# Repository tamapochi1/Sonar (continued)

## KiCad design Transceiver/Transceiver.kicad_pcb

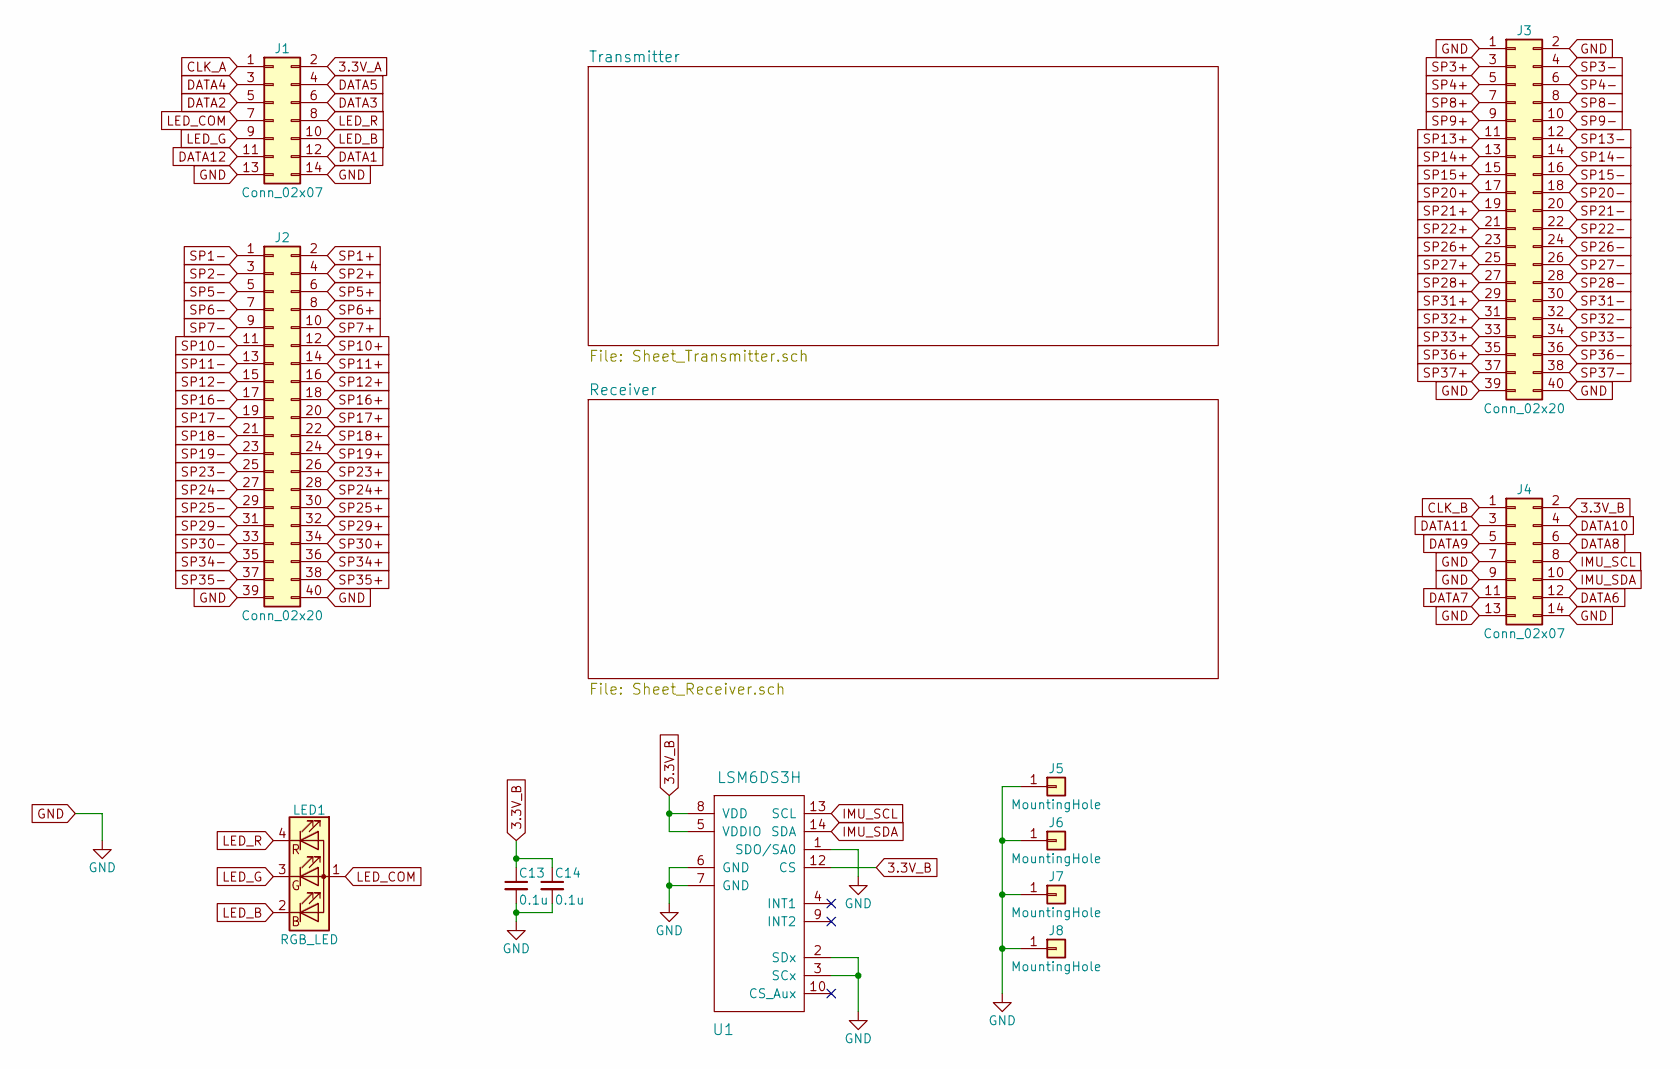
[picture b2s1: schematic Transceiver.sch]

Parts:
C13, C14: 0.1u; C_0603_HandSoldering
J1, J4: Conn_02x07; Pin_Header_Straight_2x07_Pitch2.54mm
J2, J3: Conn_02x20; Pin_Header_Straight_2x20_Pitch2.54mm
J5, J6, J7, J8: MountingHole; MountingHole_3.2mm_M3_Pad
LED1: RGB_LED; LED_Cree-PLCC4_2x2mm_CW
U1: LSM6DS3H; Bosch_LGA-14_3x2.5mm_Pitch0.5mm

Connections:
3.3V_A: J1.2; also elsewhere on the board
3.3V_B: C13.1, C14.1, J4.2, U1.5 (VDDIO), U1.8 (VDD), U1.12 (CS); also elsewhere on the board
CLK_A: J1.1; also elsewhere on the board
CLK_B: J4.1; also elsewhere on the board
DATA1: J1.12; also elsewhere on the board
DATA2: J1.5; also elsewhere on the board
DATA3: J1.6; also elsewhere on the board
DATA4: J1.3; also elsewhere on the board
DATA5: J1.4; also elsewhere on the board
DATA6: J4.12; also elsewhere on the board
DATA7: J4.11; also elsewhere on the board
DATA8: J4.6; also elsewhere on the board
DATA9: J4.5; also elsewhere on the board
DATA10: J4.4; also elsewhere on the board
DATA11: J4.3; also elsewhere on the board
DATA12: J1.11; also elsewhere on the board
GND: C13.2, C14.2, J1.13, J1.14, J2.39, J2.40, J3.1, J3.2, J3.39, J3.40, J4.7, J4.9, J4.13, J4.14, J5.1, J6.1, J7.1, J8.1, U1.1 (SDO/SA0), U1.2 (SDx), U1.3 (SCx), U1.6 (GND), U1.7 (GND); also elsewhere on the board
IMU_SCL: J4.8, U1.13 (SCL)
IMU_SDA: J4.10, U1.14 (SDA)
LED_B: J1.10, LED1.2 (BK)
LED_COM: J1.7, LED1.1 (A)
LED_G: J1.9, LED1.3 (GK)
LED_R: J1.8, LED1.4 (RK)
SP1+: J2.2; also elsewhere on the board
SP1-: J2.1; also elsewhere on the board
SP2+: J2.4; also elsewhere on the board
SP2-: J2.3; also elsewhere on the board
SP3+: J3.3; also elsewhere on the board
SP3-: J3.4; also elsewhere on the board
SP4+: J3.5; also elsewhere on the board
SP4-: J3.6; also elsewhere on the board
SP5+: J2.6; also elsewhere on the board
SP5-: J2.5; also elsewhere on the board
SP6+: J2.8; also elsewhere on the board
SP6-: J2.7; also elsewhere on the board
SP7+: J2.10; also elsewhere on the board
SP7-: J2.9; also elsewhere on the board
SP8+: J3.7; also elsewhere on the board
SP8-: J3.8; also elsewhere on the board
SP9+: J3.9; also elsewhere on the board
SP9-: J3.10; also elsewhere on the board
SP10+: J2.12; also elsewhere on the board
SP10-: J2.11; also elsewhere on the board
SP11+: J2.14; also elsewhere on the board
SP11-: J2.13; also elsewhere on the board
SP12+: J2.16; also elsewhere on the board
SP12-: J2.15; also elsewhere on the board
SP13+: J3.11; also elsewhere on the board
SP13-: J3.12; also elsewhere on the board
SP14+: J3.13; also elsewhere on the board
SP14-: J3.14; also elsewhere on the board
SP15+: J3.15; also elsewhere on the board
SP15-: J3.16; also elsewhere on the board
SP16+: J2.18; also elsewhere on the board
SP16-: J2.17; also elsewhere on the board
SP17+: J2.20; also elsewhere on the board
SP17-: J2.19; also elsewhere on the board
SP18+: J2.22; also elsewhere on the board
SP18-: J2.21; also elsewhere on the board
SP19+: J2.24; also elsewhere on the board
SP19-: J2.23; also elsewhere on the board
SP20+: J3.17; also elsewhere on the board
SP20-: J3.18; also elsewhere on the board
SP21+: J3.19; also elsewhere on the board
SP21-: J3.20; also elsewhere on the board
SP22+: J3.21; also elsewhere on the board
SP22-: J3.22; also elsewhere on the board
SP23+: J2.26; also elsewhere on the board
SP23-: J2.25; also elsewhere on the board
SP24+: J2.28; also elsewhere on the board
SP24-: J2.27; also elsewhere on the board
SP25+: J2.30; also elsewhere on the board
SP25-: J2.29; also elsewhere on the board
SP26+: J3.23; also elsewhere on the board
SP26-: J3.24; also elsewhere on the board
SP27+: J3.25; also elsewhere on the board
SP27-: J3.26; also elsewhere on the board
SP28+: J3.27; also elsewhere on the board
SP28-: J3.28; also elsewhere on the board
SP29+: J2.32; also elsewhere on the board
SP29-: J2.31; also elsewhere on the board
SP30+: J2.34; also elsewhere on the board
SP30-: J2.33; also elsewhere on the board
SP31+: J3.29; also elsewhere on the board
SP31-: J3.30; also elsewhere on the board
SP32+: J3.31; also elsewhere on the board
SP32-: J3.32; also elsewhere on the board
SP33+: J3.33; also elsewhere on the board
SP33-: J3.34; also elsewhere on the board
SP34+: J2.36; also elsewhere on the board
SP34-: J2.35; also elsewhere on the board
SP35+: J2.38; also elsewhere on the board
SP35-: J2.37; also elsewhere on the board
SP36+: J3.35; also elsewhere on the board
SP36-: J3.36; also elsewhere on the board
SP37+: J3.37; also elsewhere on the board
SP37-: J3.38; also elsewhere on the board

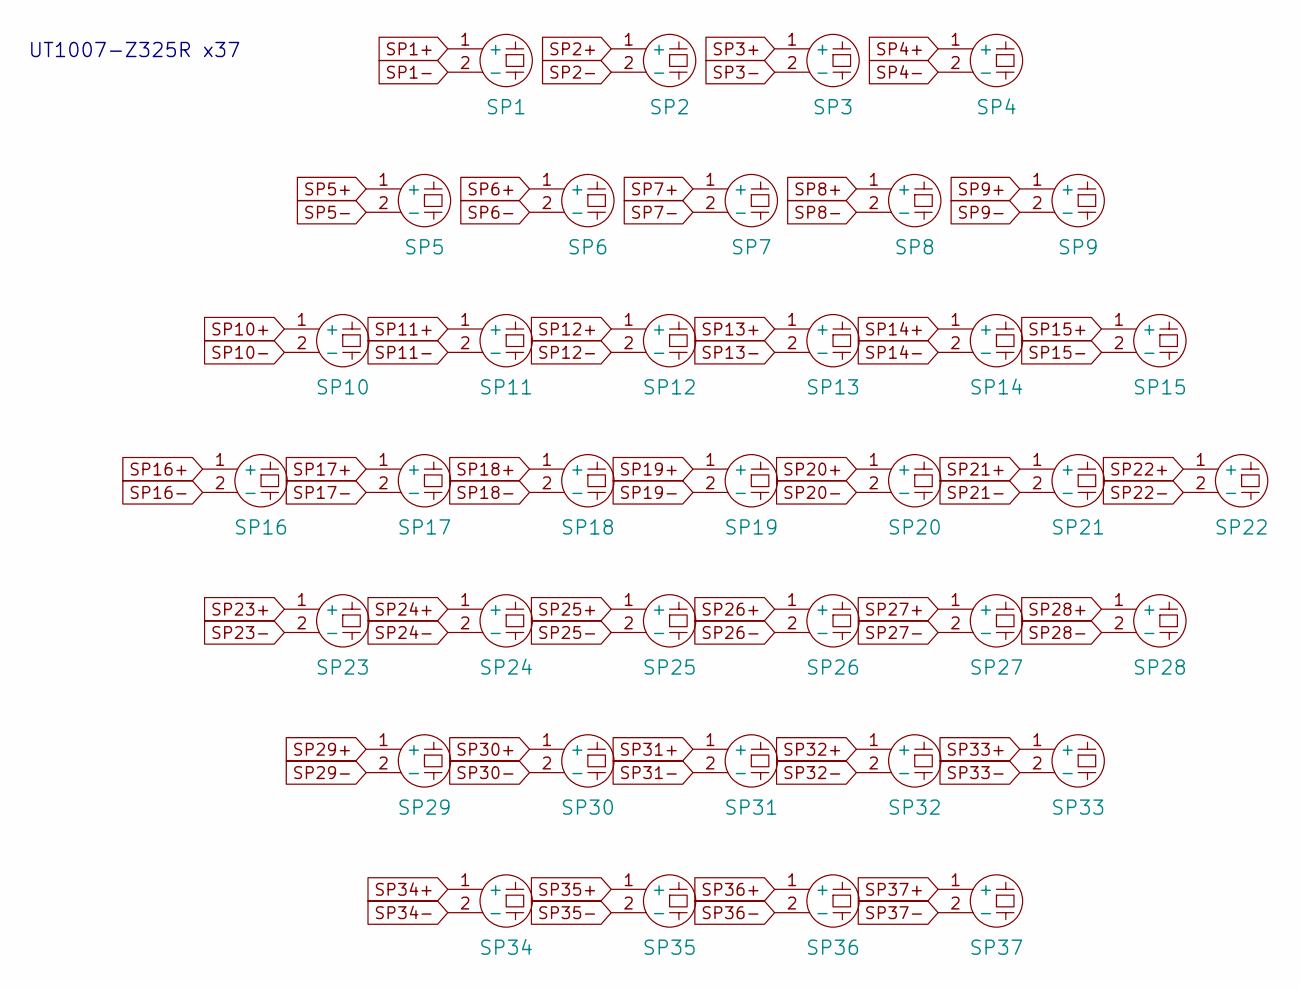
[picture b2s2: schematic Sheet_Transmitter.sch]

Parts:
SP1, SP2, SP3, SP4, SP5, SP6, SP7, SP8, SP9, SP10, SP11, SP12, SP13, SP14, SP15, SP16, SP17, SP18, SP19, SP20, SP21, SP22, SP23, SP24, SP25, SP26, SP27, SP28, SP29, SP30, SP31, SP32, SP33, SP34, SP35, SP36, SP37: UT1007-Z325R

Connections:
SP1+: SP1.1 (+); also elsewhere on the board
SP1-: SP1.2 (-); also elsewhere on the board
SP2+: SP2.1 (+); also elsewhere on the board
SP2-: SP2.2 (-); also elsewhere on the board
SP3+: SP3.1 (+); also elsewhere on the board
SP3-: SP3.2 (-); also elsewhere on the board
SP4+: SP4.1 (+); also elsewhere on the board
SP4-: SP4.2 (-); also elsewhere on the board
SP5+: SP5.1 (+); also elsewhere on the board
SP5-: SP5.2 (-); also elsewhere on the board
SP6+: SP6.1 (+); also elsewhere on the board
SP6-: SP6.2 (-); also elsewhere on the board
SP7+: SP7.1 (+); also elsewhere on the board
SP7-: SP7.2 (-); also elsewhere on the board
SP8+: SP8.1 (+); also elsewhere on the board
SP8-: SP8.2 (-); also elsewhere on the board
SP9+: SP9.1 (+); also elsewhere on the board
SP9-: SP9.2 (-); also elsewhere on the board
SP10+: SP10.1 (+); also elsewhere on the board
SP10-: SP10.2 (-); also elsewhere on the board
SP11+: SP11.1 (+); also elsewhere on the board
SP11-: SP11.2 (-); also elsewhere on the board
SP12+: SP12.1 (+); also elsewhere on the board
SP12-: SP12.2 (-); also elsewhere on the board
SP13+: SP13.1 (+); also elsewhere on the board
SP13-: SP13.2 (-); also elsewhere on the board
SP14+: SP14.1 (+); also elsewhere on the board
SP14-: SP14.2 (-); also elsewhere on the board
SP15+: SP15.1 (+); also elsewhere on the board
SP15-: SP15.2 (-); also elsewhere on the board
SP16+: SP16.1 (+); also elsewhere on the board
SP16-: SP16.2 (-); also elsewhere on the board
SP17+: SP17.1 (+); also elsewhere on the board
SP17-: SP17.2 (-); also elsewhere on the board
SP18+: SP18.1 (+); also elsewhere on the board
SP18-: SP18.2 (-); also elsewhere on the board
SP19+: SP19.1 (+); also elsewhere on the board
SP19-: SP19.2 (-); also elsewhere on the board
SP20+: SP20.1 (+); also elsewhere on the board
SP20-: SP20.2 (-); also elsewhere on the board
SP21+: SP21.1 (+); also elsewhere on the board
SP21-: SP21.2 (-); also elsewhere on the board
SP22+: SP22.1 (+); also elsewhere on the board
SP22-: SP22.2 (-); also elsewhere on the board
SP23+: SP23.1 (+); also elsewhere on the board
SP23-: SP23.2 (-); also elsewhere on the board
SP24+: SP24.1 (+); also elsewhere on the board
SP24-: SP24.2 (-); also elsewhere on the board
SP25+: SP25.1 (+); also elsewhere on the board
SP25-: SP25.2 (-); also elsewhere on the board
SP26+: SP26.1 (+); also elsewhere on the board
SP26-: SP26.2 (-); also elsewhere on the board
SP27+: SP27.1 (+); also elsewhere on the board
SP27-: SP27.2 (-); also elsewhere on the board
SP28+: SP28.1 (+); also elsewhere on the board
SP28-: SP28.2 (-); also elsewhere on the board
SP29+: SP29.1 (+); also elsewhere on the board
SP29-: SP29.2 (-); also elsewhere on the board
SP30+: SP30.1 (+); also elsewhere on the board
SP30-: SP30.2 (-); also elsewhere on the board
SP31+: SP31.1 (+); also elsewhere on the board
SP31-: SP31.2 (-); also elsewhere on the board
SP32+: SP32.1 (+); also elsewhere on the board
SP32-: SP32.2 (-); also elsewhere on the board
SP33+: SP33.1 (+); also elsewhere on the board
SP33-: SP33.2 (-); also elsewhere on the board
SP34+: SP34.1 (+); also elsewhere on the board
SP34-: SP34.2 (-); also elsewhere on the board
SP35+: SP35.1 (+); also elsewhere on the board
SP35-: SP35.2 (-); also elsewhere on the board
SP36+: SP36.1 (+); also elsewhere on the board
SP36-: SP36.2 (-); also elsewhere on the board
SP37+: SP37.1 (+); also elsewhere on the board
SP37-: SP37.2 (-); also elsewhere on the board

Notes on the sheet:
UT1007-Z325R x37

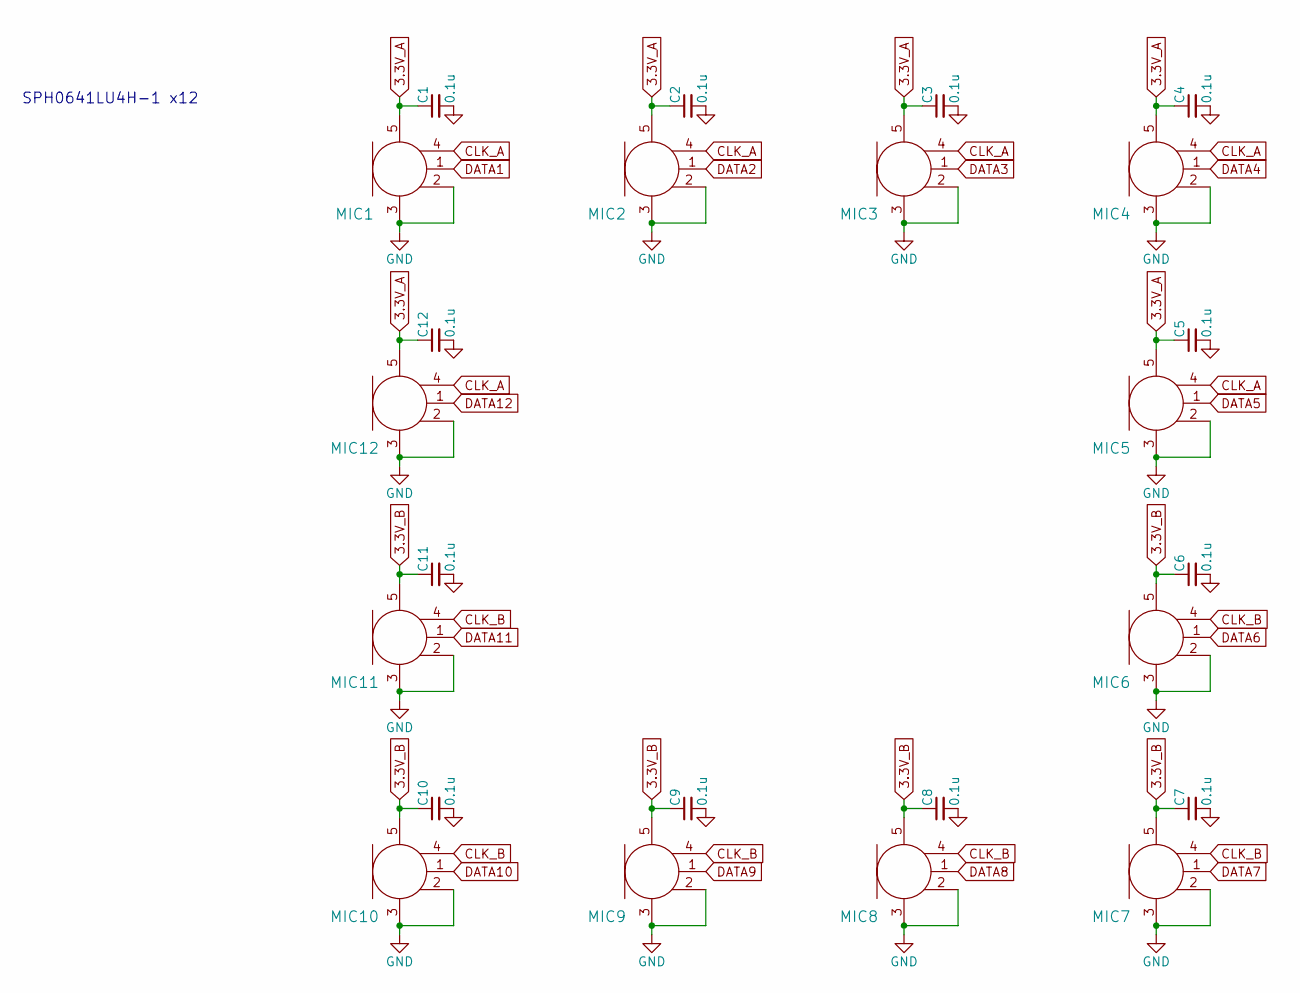
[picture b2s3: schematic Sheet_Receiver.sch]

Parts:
C1, C2, C3, C4, C5, C6, C7, C8, C9, C10, C11, C12: 0.1u; C_0603_HandSoldering
MIC1, MIC2, MIC3, MIC4, MIC5, MIC6, MIC7, MIC8, MIC9, MIC10, MIC11, MIC12: SPH0641LU4H-1

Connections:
3.3V_A: C1.1, C2.1, C3.1, C4.1, C5.1, C12.1, MIC1.5 (VDD), MIC2.5 (VDD), MIC3.5 (VDD), MIC4.5 (VDD), MIC5.5 (VDD), MIC12.5 (VDD); also elsewhere on the board
3.3V_B: C6.1, C7.1, C8.1, C9.1, C10.1, C11.1, MIC6.5 (VDD), MIC7.5 (VDD), MIC8.5 (VDD), MIC9.5 (VDD), MIC10.5 (VDD), MIC11.5 (VDD); also elsewhere on the board
CLK_A: MIC1.4 (CLOCK), MIC2.4 (CLOCK), MIC3.4 (CLOCK), MIC4.4 (CLOCK), MIC5.4 (CLOCK), MIC12.4 (CLOCK); also elsewhere on the board
CLK_B: MIC6.4 (CLOCK), MIC7.4 (CLOCK), MIC8.4 (CLOCK), MIC9.4 (CLOCK), MIC10.4 (CLOCK), MIC11.4 (CLOCK); also elsewhere on the board
DATA1: MIC1.1 (DATA); also elsewhere on the board
DATA2: MIC2.1 (DATA); also elsewhere on the board
DATA3: MIC3.1 (DATA); also elsewhere on the board
DATA4: MIC4.1 (DATA); also elsewhere on the board
DATA5: MIC5.1 (DATA); also elsewhere on the board
DATA6: MIC6.1 (DATA); also elsewhere on the board
DATA7: MIC7.1 (DATA); also elsewhere on the board
DATA8: MIC8.1 (DATA); also elsewhere on the board
DATA9: MIC9.1 (DATA); also elsewhere on the board
DATA10: MIC10.1 (DATA); also elsewhere on the board
DATA11: MIC11.1 (DATA); also elsewhere on the board
DATA12: MIC12.1 (DATA); also elsewhere on the board
GND: C1.2, C2.2, C3.2, C4.2, C5.2, C6.2, C7.2, C8.2, C9.2, C10.2, C11.2, C12.2, MIC1.2 (SELECT), MIC1.3 (GND), MIC2.2 (SELECT), MIC2.3 (GND), MIC3.2 (SELECT), MIC3.3 (GND), MIC4.2 (SELECT), MIC4.3 (GND), MIC5.2 (SELECT), MIC5.3 (GND), MIC6.2 (SELECT), MIC6.3 (GND), MIC7.2 (SELECT), MIC7.3 (GND), MIC8.2 (SELECT), MIC8.3 (GND), MIC9.2 (SELECT), MIC9.3 (GND), MIC10.2 (SELECT), MIC10.3 (GND), MIC11.2 (SELECT), MIC11.3 (GND), MIC12.2 (SELECT), MIC12.3 (GND); also elsewhere on the board

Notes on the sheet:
SPH0641LU4H-1 x12

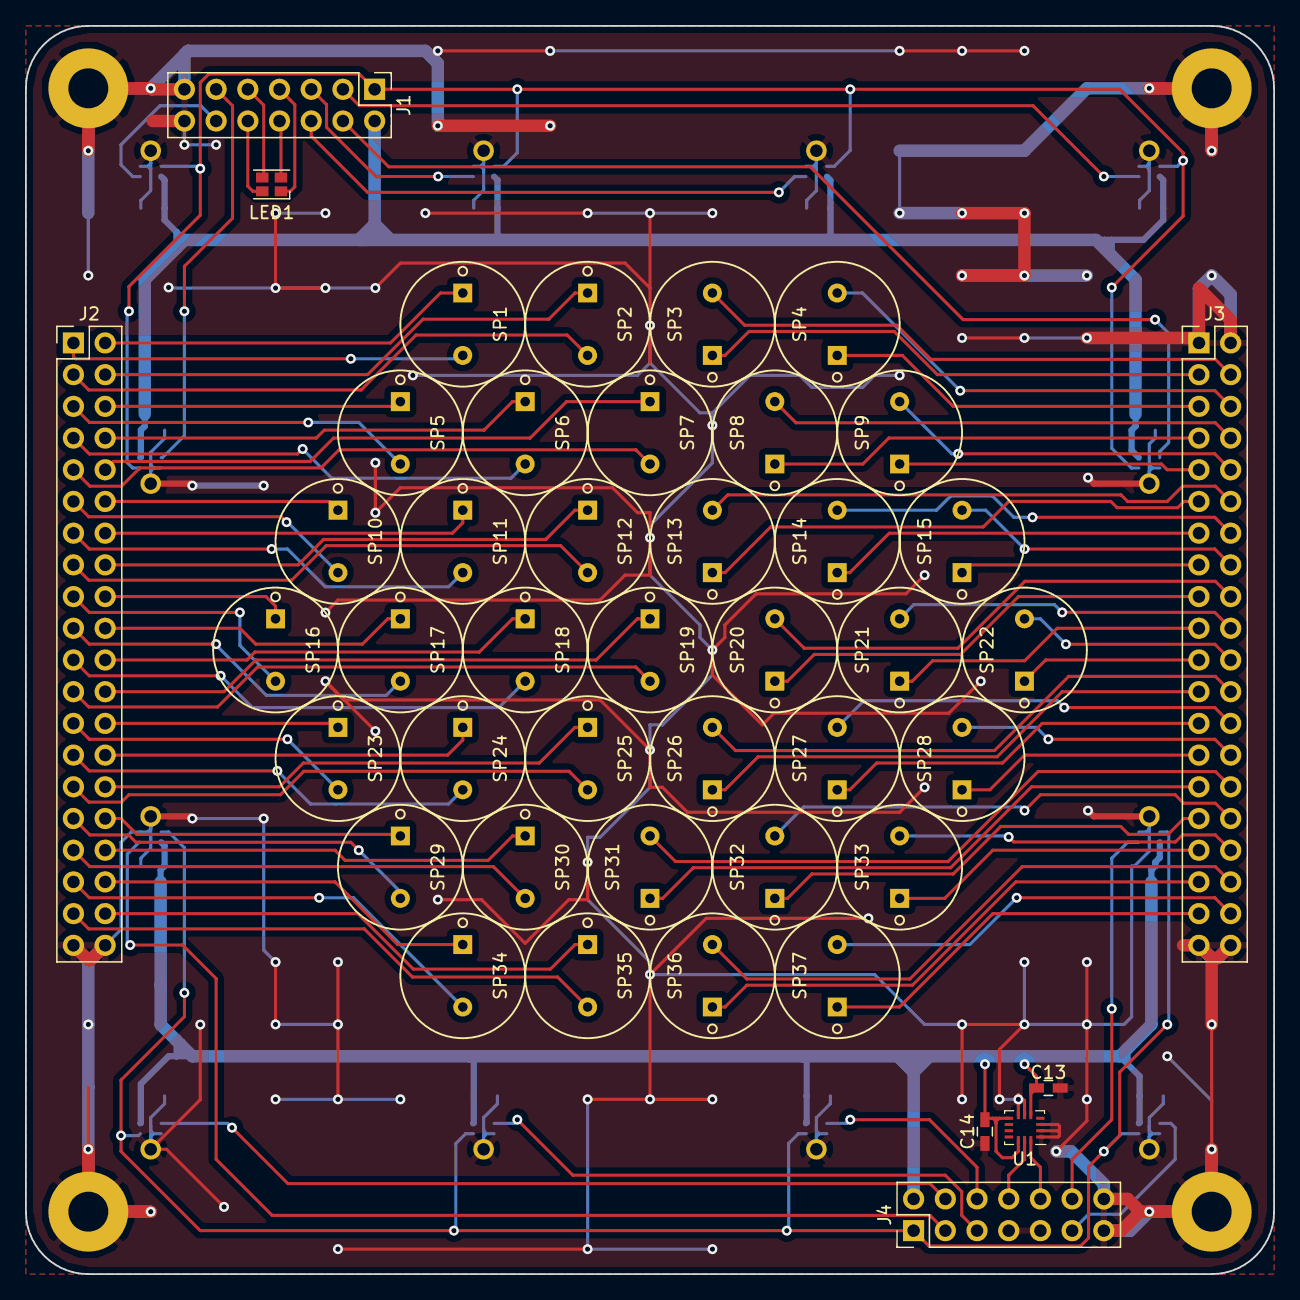
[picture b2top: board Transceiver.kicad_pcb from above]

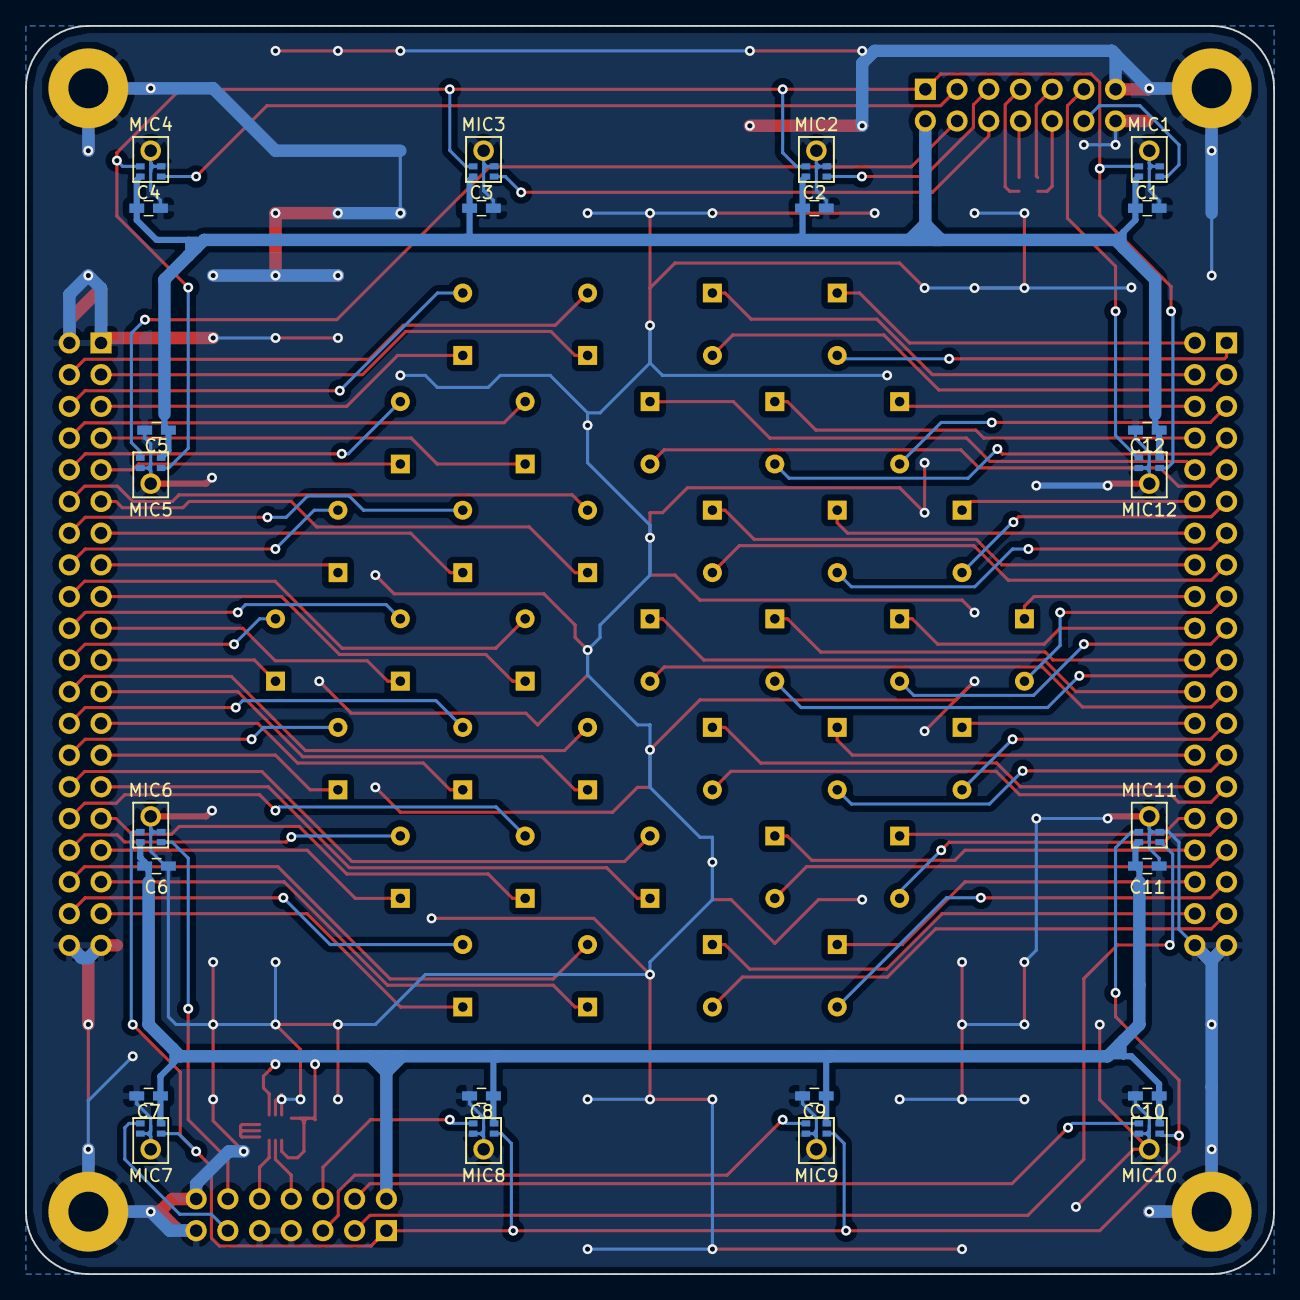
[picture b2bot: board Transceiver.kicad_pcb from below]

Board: 2 copper layers, 100.0 x 100.0 mm, 73 parts (24 on the bottom side), 97 nets.

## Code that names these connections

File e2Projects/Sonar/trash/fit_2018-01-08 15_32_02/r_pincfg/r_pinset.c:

/***********************************************************************************************************************
* DISCLAIMER
* This software is supplied by Renesas Electronics Corporation and is only intended for use with Renesas products.
* No other uses are authorized. This software is owned by Renesas Electronics Corporation and is protected under all
* applicable laws, including copyright laws. 
* THIS SOFTWARE IS PROVIDED "AS IS" AND RENESAS MAKES NO WARRANTIESREGARDING THIS SOFTWARE, WHETHER EXPRESS, IMPLIED
* OR STATUTORY, INCLUDING BUT NOT LIMITED TO WARRANTIES OF MERCHANTABILITY, FITNESS FOR A PARTICULAR PURPOSE AND
* NON-INFRINGEMENT.  ALL SUCH WARRANTIES ARE EXPRESSLY DISCLAIMED.TO THE MAXIMUM EXTENT PERMITTED NOT PROHIBITED BY
* LAW, NEITHER RENESAS ELECTRONICS CORPORATION NOR ANY OF ITS AFFILIATED COMPANIES SHALL BE LIABLE FOR ANY DIRECT,
* INDIRECT, SPECIAL, INCIDENTAL OR CONSEQUENTIAL DAMAGES FOR ANY REASON RELATED TO THIS SOFTWARE, EVEN IF RENESAS OR
* ITS AFFILIATES HAVE BEEN ADVISED OF THE POSSIBILITY OF SUCH DAMAGES.
* Renesas reserves the right, without notice, to make changes to this software and to discontinue the availability 
* of this software. By using this software, you agree to the additional terms and conditions found by accessing the 
* following link:
* http://www.renesas.com/disclaimer
*
* Copyright (C) 2018 Renesas Electronics Corporation. All rights reserved.
***********************************************************************************************************************/
/***********************************************************************************************************************
* File Name    : r_pinset.c
* Version      : 1.2.3
* Device(s)    : R5F571MFDxFB
* Tool-Chain   : RXC
* Description  : Setting of port and mpc registers
* Creation Date: 07 1 2018
***********************************************************************************************************************/

/***********************************************************************************************************************
Includes
***********************************************************************************************************************/
#include "r_pinset.h"
#include "platform.h"

/***********************************************************************************************************************
Global variables and functions
***********************************************************************************************************************/
/***********************************************************************************************************************
* Function Name: R_PDC_PinSet
* Description  : This function initializes pins for r_pdc_rx module
* Arguments    : none
* Return Value : none
***********************************************************************************************************************/
void R_PDC_PinSet()
{
    R_BSP_RegisterProtectDisable(BSP_REG_PROTECT_MPC);

    /* Set PIXCLK pin */
    MPC.P24PFS.BYTE = 0x1CU;
    PORT2.PMR.BIT.B4 = 1U;

    /* Set VSYNC pin */
    MPC.P32PFS.BYTE = 0x1CU;
    PORT3.PMR.BIT.B2 = 1U;

    /* Set HSYNC pin */
    MPC.P25PFS.BYTE = 0x1CU;
    PORT2.PMR.BIT.B5 = 1U;

    /* Set PIXD7 pin */
    MPC.P23PFS.BYTE = 0x1CU;
    PORT2.PMR.BIT.B3 = 1U;

    /* Set PIXD6 pin */
    MPC.P22PFS.BYTE = 0x1CU;
    PORT2.PMR.BIT.B2 = 1U;

    /* Set PIXD5 pin */
    MPC.P21PFS.BYTE = 0x1CU;
    PORT2.PMR.BIT.B1 = 1U;

    /* Set PIXD4 pin */
    MPC.P20PFS.BYTE = 0x1CU;
    PORT2.PMR.BIT.B0 = 1U;

    /* Set PIXD3 pin */
    MPC.P17PFS.BYTE = 0x1CU;
    PORT1.PMR.BIT.B7 = 1U;

    /* Set PIXD2 pin */
    MPC.P87PFS.BYTE = 0x1CU;
    PORT8.PMR.BIT.B7 = 1U;

    /* Set PIXD1 pin */
    MPC.P86PFS.BYTE = 0x1CU;
    PORT8.PMR.BIT.B6 = 1U;

    /* Set PIXD0 pin */
    MPC.P15PFS.BYTE = 0x1CU;
    PORT1.PMR.BIT.B5 = 1U;

    /* Set PCKO pin */
    MPC.P33PFS.BYTE = 0x1CU;
    PORT3.PMR.BIT.B3 = 1U;

    R_BSP_RegisterProtectEnable(BSP_REG_PROTECT_MPC);
}

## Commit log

2017-10-01 :tada: Added .gitattributes
2017-10-08 超音波送受信テストボードを追加
    PCBGOGOに基板を発注
2017-10-11 テストボード用FPGAコードを追加
    超音波送信機能、CIC、FIR、その他
2017-10-16 CICフィルタ変更、シミュレーション実行、.gitignore追加
2017-10-18 ドキュメント追加
2017-10-23 超音波トランシーバ基板追加
2017-10-30 gitignore変更
2017-10-30 テストボード動作確認、実験
2017-11-10 実験結果のグラフを出図
2017-11-12 トランシーバ基板にLEDとIMUを追加
2017-11-12 トランシーバ基板シルク修正
2017-12-07 トランシーバ基板修正
2017-12-07 メインボード回路設計・フットプリント配置
2017-12-17 メインボード完成
2017-12-17 トランシーバ基板修正
    シルクの位置修正
2017-12-18 ソナー基板入稿
2018-01-04 MCU、FPGAのプロジェクト追加
2018-01-04 git ignore変更
2018-01-04 gitignore変更によりe2のプロジェクトをコミット
2018-03-21 超音波の送受信を行えるようにした
